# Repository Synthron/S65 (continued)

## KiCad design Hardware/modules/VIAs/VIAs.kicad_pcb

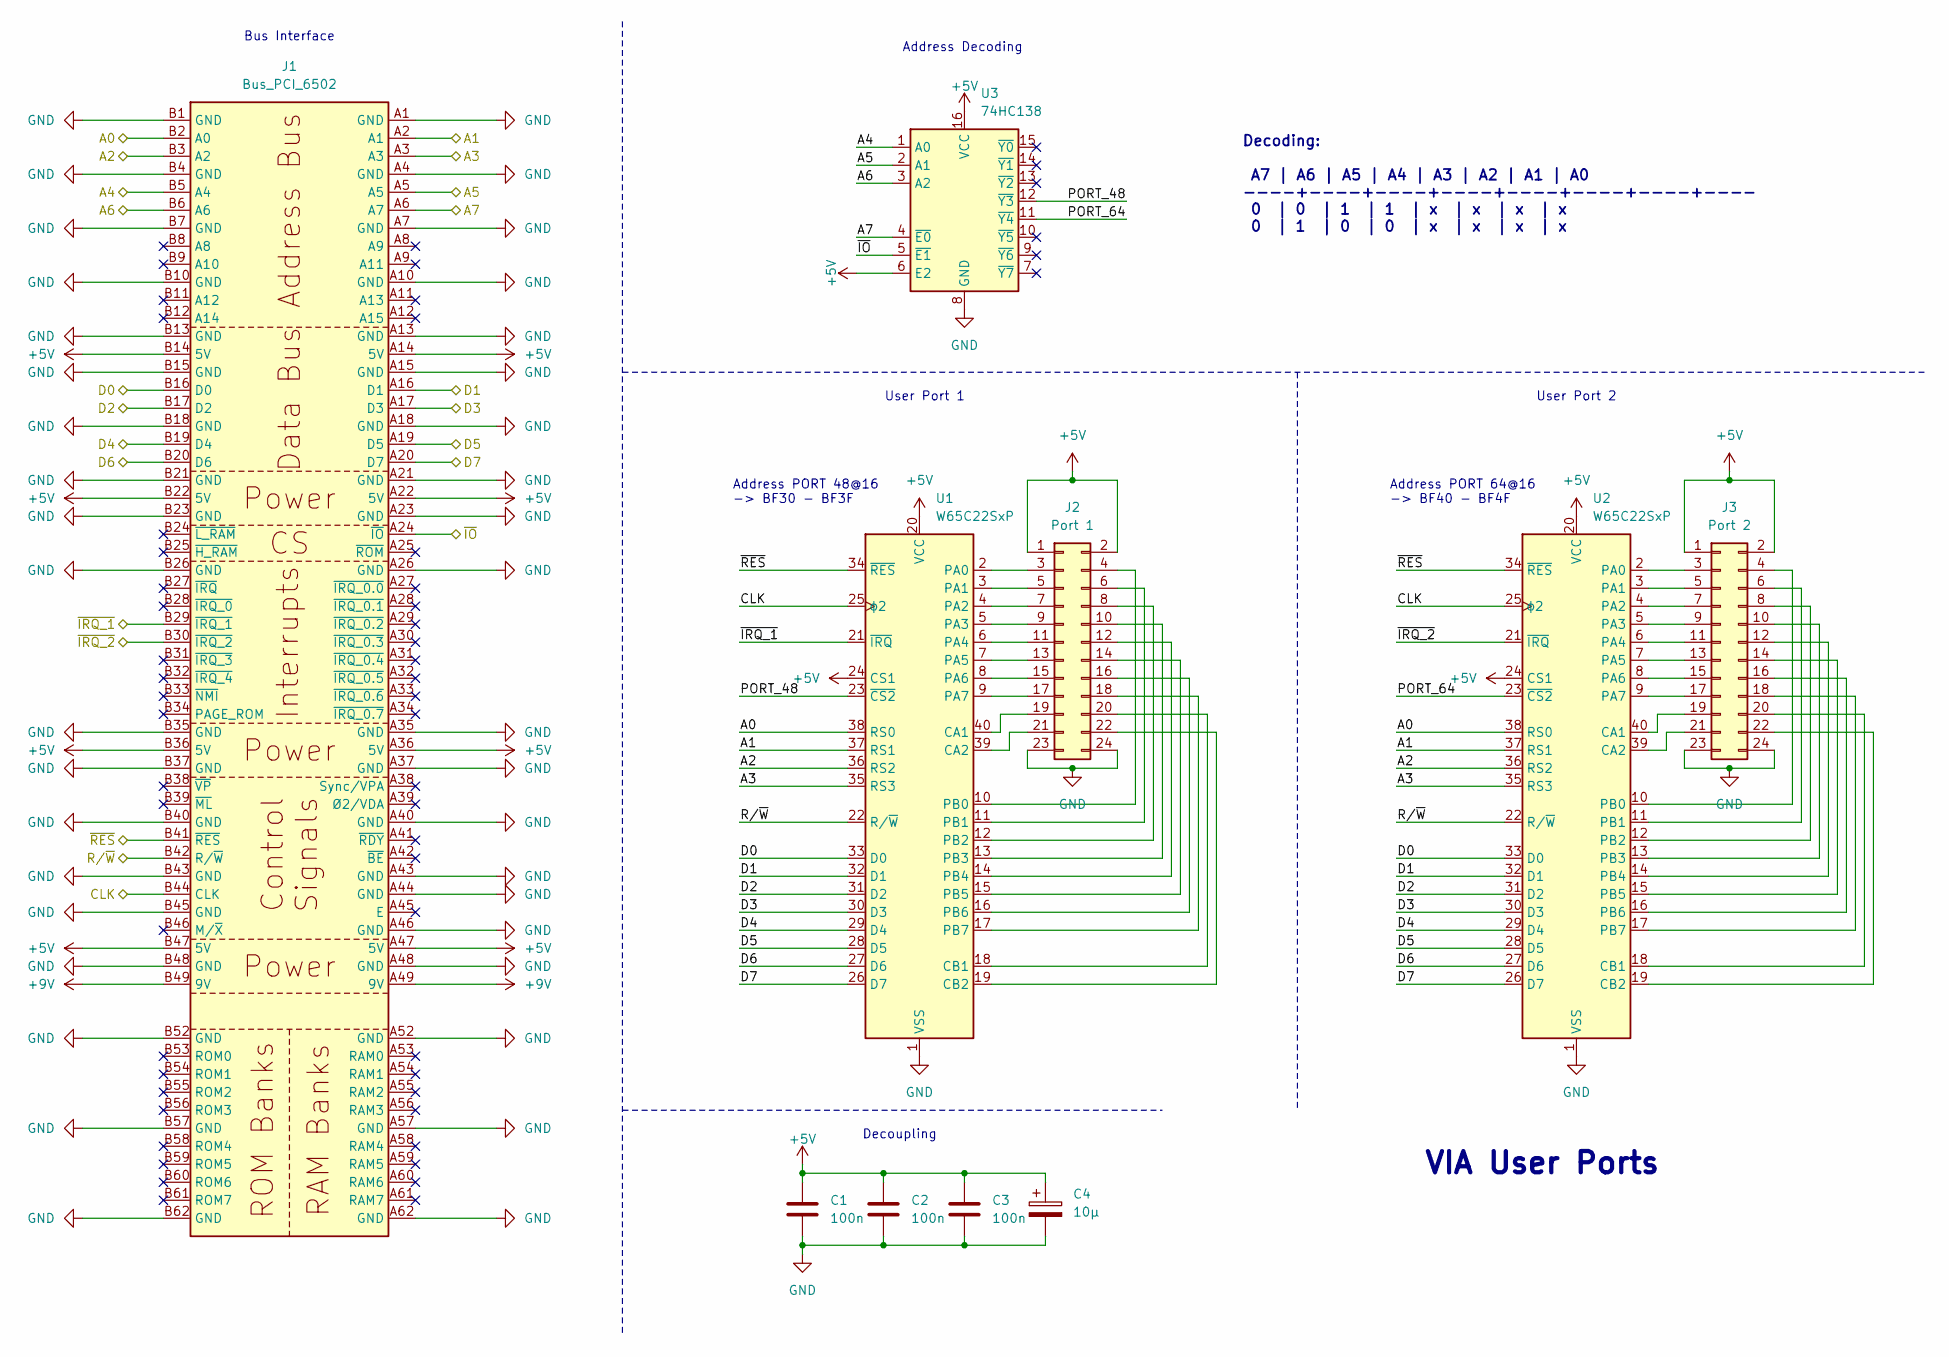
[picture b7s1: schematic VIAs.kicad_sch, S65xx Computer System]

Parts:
C1, C2, C3: 100n; C_0805_2012Metric
C4: 10µ; CP_Radial_D5.0mm_P2.50mm
J1: Bus_PCI_6502; BUS_PCI
J2: Port 1; Pin_Header_2x12
J3: Port 2; Pin_Header_2x12
U1, U2: W65C22SxP; DIP-40_W15.24mm
U3: 74HC138; DIP-16_W7.62mm_LongPads

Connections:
+5V: C1.1, C2.1, C3.1, C4.1, J1.A14 (5V), J1.A22 (5V), J1.A36 (5V), J1.A47 (5V), J1.B14 (5V), J1.B22 (5V), J1.B36 (5V), J1.B47 (5V), J2.1, J2.2, J3.1, J3.2, U1.20 (VCC), U1.24 (CS1), U2.20 (VCC), U2.24 (CS1), U3.6 (E2), U3.16 (VCC)
+9V: J1.A49 (9V), J1.B49 (9V)
/A0: J1.B2 (A0), U1.38 (RS0), U2.38 (RS0)
/A1: J1.A2 (A1), U1.37 (RS1), U2.37 (RS1)
/A2: J1.B3 (A2), U1.36 (RS2), U2.36 (RS2)
/A3: J1.A3, U1.35 (RS3), U2.35 (RS3)
/A4: J1.B5 (A4), U3.1 (A0)
/A5: J1.A5, U3.2 (A1)
/A6: J1.B6 (A6), U3.3 (A2)
/A7: J1.A6 (A7), U3.4 (~E0)
/CLK: J1.B44 (CLK), U1.25 (ϕ2), U2.25 (ϕ2)
/D0: J1.B16 (D0), U1.33 (D0), U2.33 (D0)
/D1: J1.A16 (D1), U1.32 (D1), U2.32 (D1)
/D2: J1.B17 (D2), U1.31 (D2), U2.31 (D2)
/D3: J1.A17 (D3), U1.30 (D3), U2.30 (D3)
/D4: J1.B19 (D4), U1.29 (D4), U2.29 (D4)
/D5: J1.A19 (D5), U1.28 (D5), U2.28 (D5)
/D6: J1.B20 (D6), U1.27 (D6), U2.27 (D6)
/D7: J1.A20 (D7), U1.26 (D7), U2.26 (D7)
/PORT_48: U1.23 (~CS2), U3.12 (~Y3)
/PORT_64: U2.23 (~CS2), U3.11 (~Y4)
/R/~W: J1.B42 (R/~W), U1.22 (R/~W), U2.22 (R/~W)
/~IO: J1.A24 (~IO), U3.5 (~E1)
/~IRQ_1: J1.B29 (~IRQ_1), U1.21 (~IRQ)
/~IRQ_2: J1.B30 (~IRQ_2), U2.21 (~IRQ)
/~RES: J1.B41 (~RES), U1.34 (~RES), U2.34 (~RES)
GND: C1.2, C2.2, C3.2, C4.2, J1.A1 (GND), J1.A4 (GND), J1.A7 (GND), J1.A10 (GND), J1.A13 (GND), J1.A15 (GND), J1.A18 (GND), J1.A21 (GND), J1.A23 (GND), J1.A26 (GND), J1.A35 (GND), J1.A37 (GND), J1.A40 (GND), J1.A43 (GND), J1.A44 (GND), J1.A46 (GND), J1.A48 (GND), J1.A52 (GND), J1.A57 (GND), J1.A62 (GND), J1.B1 (GND), J1.B4 (GND), J1.B7 (GND), J1.B10 (GND), J1.B13 (GND), J1.B15 (GND), J1.B18 (GND), J1.B21 (GND), J1.B23 (GND), J1.B26 (GND), J1.B35 (GND), J1.B37 (GND), J1.B40 (GND), J1.B43 (GND), J1.B45 (GND), J1.B48 (GND), J1.B52 (GND), J1.B57 (GND), J1.B62 (GND), J2.23, J2.24, J3.23, J3.24, U1.1 (VSS), U2.1 (VSS), U3.8 (GND)
unnamed: J2.3, U1.2 (PA0)
unnamed: J2.4, U1.10 (PB0)
unnamed: J2.5, U1.3 (PA1)
unnamed: J2.6, U1.11 (PB1)
unnamed: J2.7, U1.4 (PA2)
unnamed: J2.8, U1.12 (PB2)
unnamed: J2.9, U1.5 (PA3)
unnamed: J2.10, U1.13 (PB3)
unnamed: J2.11, U1.6 (PA4)
unnamed: J2.12, U1.14 (PB4)
unnamed: J2.13, U1.7 (PA5)
unnamed: J2.14, U1.15 (PB5)
unnamed: J2.15, U1.8 (PA6)
unnamed: J2.16, U1.16 (PB6)
unnamed: J2.17, U1.9 (PA7)
unnamed: J2.18, U1.17 (PB7)
unnamed: J2.19, U1.40 (CA1)
unnamed: J2.20, U1.18 (CB1)
unnamed: J2.21, U1.39 (CA2)
unnamed: J2.22, U1.19 (CB2)
unnamed: J3.3, U2.2 (PA0)
unnamed: J3.4, U2.10 (PB0)
unnamed: J3.5, U2.3 (PA1)
unnamed: J3.6, U2.11 (PB1)
unnamed: J3.7, U2.4 (PA2)
unnamed: J3.8, U2.12 (PB2)
unnamed: J3.9, U2.5 (PA3)
unnamed: J3.10, U2.13 (PB3)
unnamed: J3.11, U2.6 (PA4)
unnamed: J3.12, U2.14 (PB4)
unnamed: J3.13, U2.7 (PA5)
unnamed: J3.14, U2.15 (PB5)
unnamed: J3.15, U2.8 (PA6)
unnamed: J3.16, U2.16 (PB6)
unnamed: J3.17, U2.9 (PA7)
unnamed: J3.18, U2.17 (PB7)
unnamed: J3.19, U2.40 (CA1)
unnamed: J3.20, U2.18 (CB1)
unnamed: J3.21, U2.39 (CA2)
unnamed: J3.22, U2.19 (CB2)

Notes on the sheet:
Bus Interface
Address PORT 64@16 -> BF40 - BF4F
Decoding: A7 | A6 | A5 | A4 | A3 | A2 | A1 | A0 ----+----+----+----+----+----+----+---- 0 | 0 | 1 | 1 | x | x | x | x 0 | 1 | 0 | 0 | x | x | x | x
User Port 1
Address Decoding
Decoupling
VIA User Ports
User Port 2
Address PORT 48@16 -> BF30 - BF3F

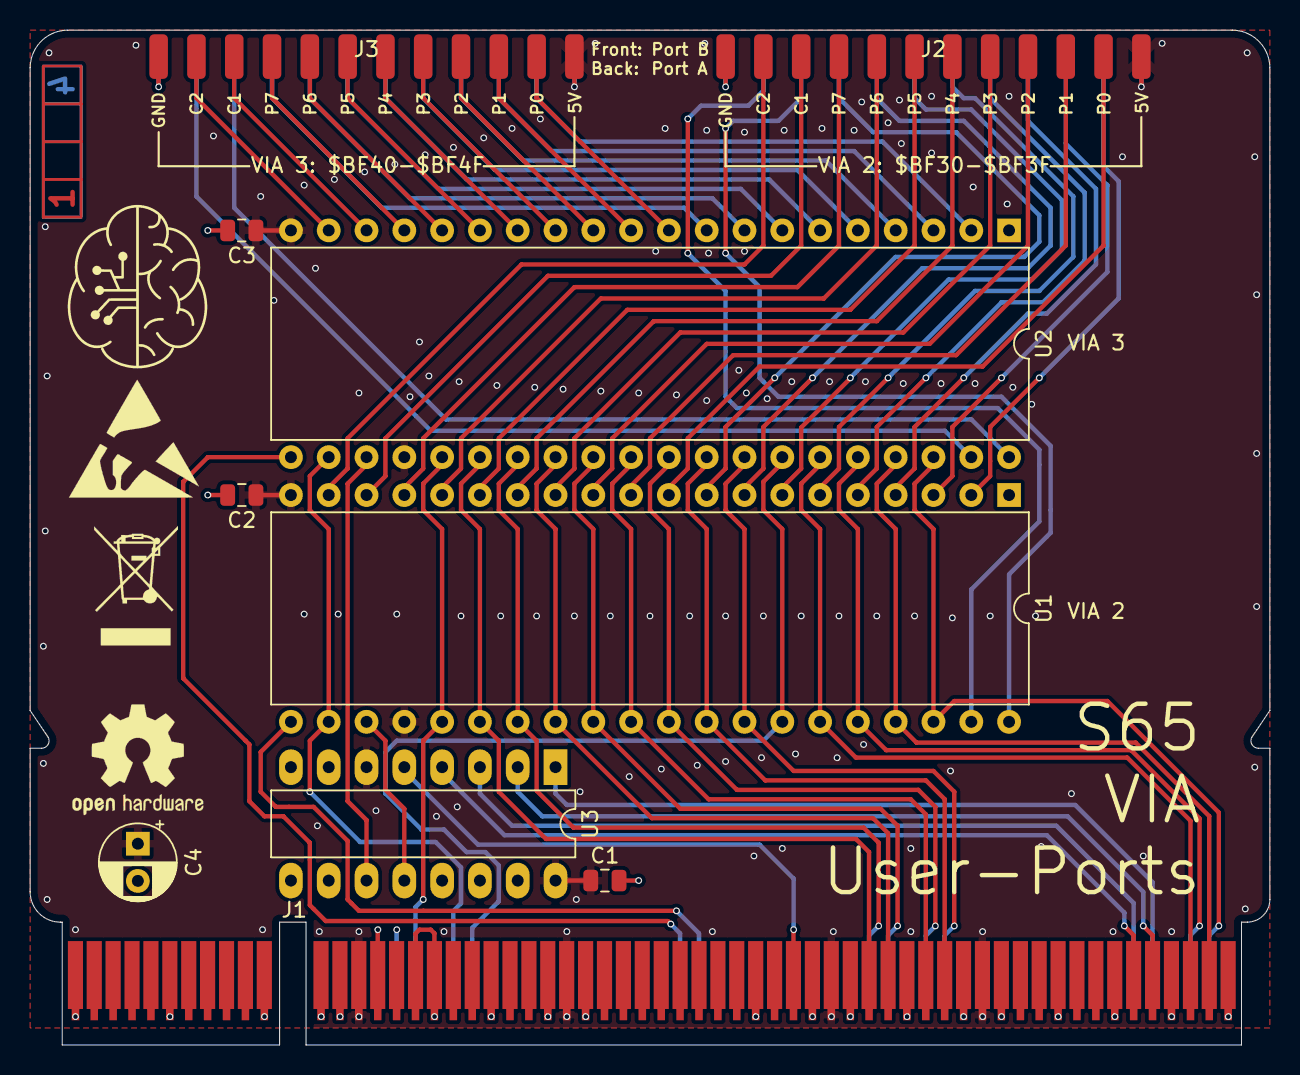
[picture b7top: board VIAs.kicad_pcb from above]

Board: 4 copper layers, 83.3 x 68.2 mm, 11 parts (1 on the bottom side), 67 nets.

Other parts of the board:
Ref**: Val**; ladder_4

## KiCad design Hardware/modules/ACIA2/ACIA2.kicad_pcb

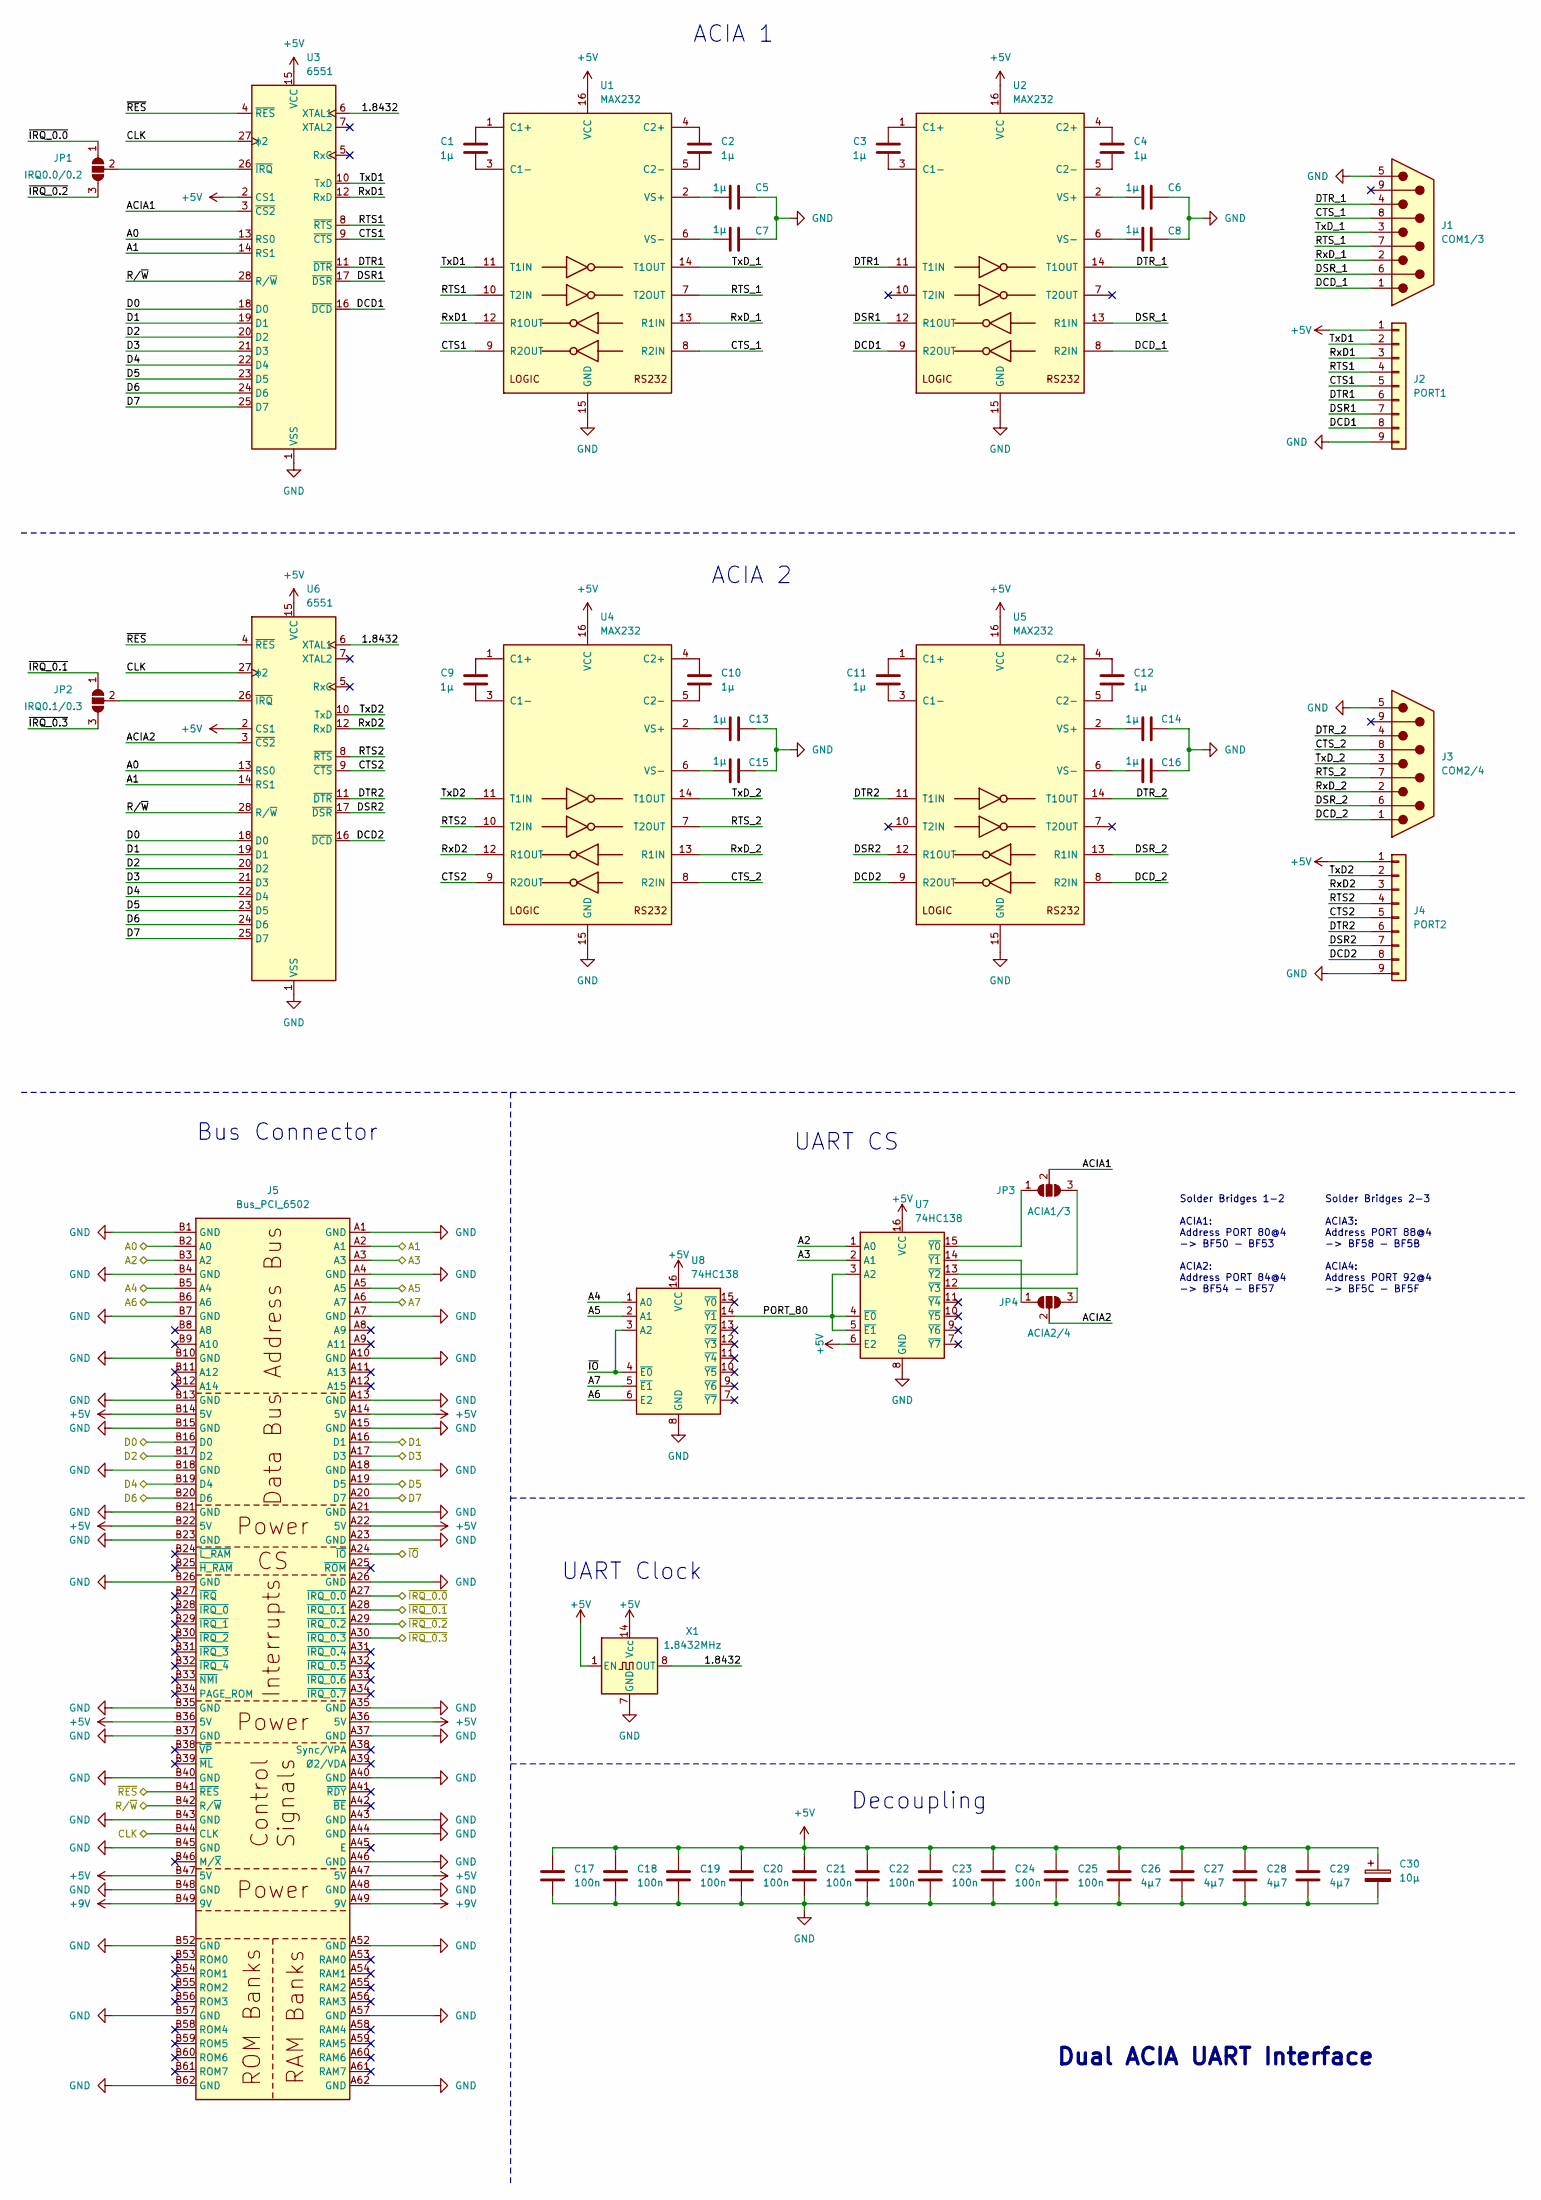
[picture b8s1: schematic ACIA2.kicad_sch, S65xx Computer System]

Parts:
C1, C2, C3, C4, C5, C6, C7, C8, C9, C10, C11, C12, C13, C14, C15, C16: 1µ; C_0805_2012Metric
C17, C18, C19, C20, C21, C22, C23, C24, C25: 100n; C_0805_2012Metric
C26, C27, C28, C29: 4µ7; C_0805_2012Metric
C30: 10µ; CP_Radial_D5.0mm_P2.50mm
J1: COM1/3; DSUB-9_Male_EdgeMount_P2.77mm
J2: PORT1; PinHeader_1x09_P2.54mm_Vertical
J3: COM2/4; DSUB-9_Male_EdgeMount_P2.77mm
J4: PORT2; PinHeader_1x09_P2.54mm_Vertical
J5: Bus_PCI_6502; BUS_PCI
JP1: IRQ0.0/0.2; SolderJumper-3_P2.0mm_Open_TrianglePad1.0x1.5mm_NumberLabels
JP2: IRQ0.1/0.3; SolderJumper-3_P2.0mm_Open_TrianglePad1.0x1.5mm_NumberLabels
JP3: ACIA1/3; SolderJumper-3_P2.0mm_Open_TrianglePad1.0x1.5mm_NumberLabels
JP4: ACIA2/4; SolderJumper-3_P2.0mm_Open_TrianglePad1.0x1.5mm_NumberLabels
U1, U2, U4, U5: MAX232; DIP-16_W7.62mm
U3, U6: 6551; DIP-28_W15.24mm
U7, U8: 74HC138; DIP-16_W7.62mm
X1: 1.8432MHz; Oscillator_DIP-14

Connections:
+5V: C17.1, C18.1, C19.1, C20.1, C21.1, C22.1, C23.1, C24.1, C25.1, C26.1, C27.1, C28.1, C29.1, C30.1, J2.1, J4.1, J5.A14 (5V), J5.A22 (5V), J5.A36 (5V), J5.A47 (5V), J5.B14 (5V), J5.B22 (5V), J5.B36 (5V), J5.B47 (5V), U1.16 (VCC), U2.16 (VCC), U3.2 (CS1), U3.15 (VCC), U4.16 (VCC), U5.16 (VCC), U6.2 (CS1), U6.15 (VCC), U7.6 (E2), U7.16 (VCC), U8.16 (VCC), X1.1 (EN), X1.14 (Vcc)
+9V: J5.A49 (9V), J5.B49 (9V)
/1.8432: U3.6 (XTAL1), U6.6 (XTAL1), X1.8 (OUT)
/A0: J5.B2 (A0), U3.13 (RS0), U6.13 (RS0)
/A1: J5.A2 (A1), U3.14 (RS1), U6.14 (RS1)
/A2: J5.B3 (A2), U7.1 (A0)
/A3: J5.A3, U7.2 (A1)
/A4: J5.B5 (A4), U8.1 (A0)
/A5: J5.A5, U8.2 (A1)
/A6: J5.B6 (A6), U8.6 (E2)
/A7: J5.A6 (A7), U8.5 (~E1)
/ACIA1: JP3.2 (C), U3.3 (~CS2)
/ACIA2: JP4.2 (C), U6.3 (~CS2)
/CLK: J5.B44 (CLK), U3.27 (ϕ2), U6.27 (ϕ2)
/CTS1: J2.5, U1.9 (R2OUT), U3.9 (~CTS)
/CTS2: J4.5, U4.9 (R2OUT), U6.9 (~CTS)
/CTS_1: J1.8, U1.8 (R2IN)
/CTS_2: J3.8, U4.8 (R2IN)
/D0: J5.B16 (D0), U3.18 (D0), U6.18 (D0)
/D1: J5.A16 (D1), U3.19 (D1), U6.19 (D1)
/D2: J5.B17 (D2), U3.20 (D2), U6.20 (D2)
/D3: J5.A17 (D3), U3.21 (D3), U6.21 (D3)
/D4: J5.B19 (D4), U3.22 (D4), U6.22 (D4)
/D5: J5.A19 (D5), U3.23 (D5), U6.23 (D5)
/D6: J5.B20 (D6), U3.24 (D6), U6.24 (D6)
/D7: J5.A20 (D7), U3.25 (D7), U6.25 (D7)
/DCD1: J2.8, U2.9 (R2OUT), U3.16 (~DCD)
/DCD2: J4.8, U5.9 (R2OUT), U6.16 (~DCD)
/DCD_1: J1.1, U2.8 (R2IN)
/DCD_2: J3.1, U5.8 (R2IN)
/DSR1: J2.7, U2.12 (R1OUT), U3.17 (~DSR)
/DSR2: J4.7, U5.12 (R1OUT), U6.17 (~DSR)
/DSR_1: J1.6, U2.13 (R1IN)
/DSR_2: J3.6, U5.13 (R1IN)
/DTR1: J2.6, U2.11 (T1IN), U3.11 (~DTR)
/DTR2: J4.6, U5.11 (T1IN), U6.11 (~DTR)
/DTR_1: J1.4, U2.14 (T1OUT)
/DTR_2: J3.4, U5.14 (T1OUT)
/PORT_80: U7.3 (A2), U7.4 (~E0), U7.5 (~E1), U8.14 (~Y1)
/RTS1: J2.4, U1.10 (T2IN), U3.8 (~RTS)
/RTS2: J4.4, U4.10 (T2IN), U6.8 (~RTS)
/RTS_1: J1.7, U1.7 (T2OUT)
/RTS_2: J3.7, U4.7 (T2OUT)
/RxD1: J2.3, U1.12 (R1OUT), U3.12 (RxD)
/RxD2: J4.3, U4.12 (R1OUT), U6.12 (RxD)
/RxD_1: J1.2, U1.13 (R1IN)
/RxD_2: J3.2, U4.13 (R1IN)
/R/~W: J5.B42 (R/~W), U3.28 (R/~W), U6.28 (R/~W)
/TxD1: J2.2, U1.11 (T1IN), U3.10 (TxD)
/TxD2: J4.2, U4.11 (T1IN), U6.10 (TxD)
/TxD_1: J1.3, U1.14 (T1OUT)
/TxD_2: J3.3, U4.14 (T1OUT)
/~IO: J5.A24 (~IO), U8.3 (A2), U8.4 (~E0)
/~IRQ_0.0: J5.A27 (~IRQ_0.0), JP1.1 (A)
/~IRQ_0.1: J5.A28 (~IRQ_0.1), JP2.1 (A)
/~IRQ_0.2: J5.A29 (~IRQ_0.2), JP1.3 (B)
/~IRQ_0.3: J5.A30 (~IRQ_0.3), JP2.3 (B)
/~RES: J5.B41 (~RES), U3.4 (~RES), U6.4 (~RES)
GND: C5.2, C6.2, C7.2, C8.2, C13.2, C14.2, C15.2, C16.2, C17.2, C18.2, C19.2, C20.2, C21.2, C22.2, C23.2, C24.2, C25.2, C26.2, C27.2, C28.2, C29.2, C30.2, J1.5, J2.9, J3.5, J4.9, J5.A1 (GND), J5.A4 (GND), J5.A7 (GND), J5.A10 (GND), J5.A13 (GND), J5.A15 (GND), J5.A18 (GND), J5.A21 (GND), J5.A23 (GND), J5.A26 (GND), J5.A35 (GND), J5.A37 (GND), J5.A40 (GND), J5.A43 (GND), J5.A44 (GND), J5.A46 (GND), J5.A48 (GND), J5.A52 (GND), J5.A57 (GND), J5.A62 (GND), J5.B1 (GND), J5.B4 (GND), J5.B7 (GND), J5.B10 (GND), J5.B13 (GND), J5.B15 (GND), J5.B18 (GND), J5.B21 (GND), J5.B23 (GND), J5.B26 (GND), J5.B35 (GND), J5.B37 (GND), J5.B40 (GND), J5.B43 (GND), J5.B45 (GND), J5.B48 (GND), J5.B52 (GND), J5.B57 (GND), J5.B62 (GND), U1.15 (GND), U2.15 (GND), U3.1 (VSS), U4.15 (GND), U5.15 (GND), U6.1 (VSS), U7.8 (GND), U8.8 (GND), X1.7 (GND)
unnamed: JP1.2 (C), U3.26 (~IRQ)
unnamed: JP2.2 (C), U6.26 (~IRQ)
unnamed: JP3.1 (A), U7.15 (~Y0)
unnamed: JP3.3 (B), U7.13 (~Y2)
unnamed: JP4.1 (A), U7.14 (~Y1)
unnamed: JP4.3 (B), U7.12 (~Y3)
unnamed: C1.1, U1.1 (C1+)
unnamed: C1.2, U1.3 (C1-)
unnamed: C2.1, U1.4 (C2+)
unnamed: C2.2, U1.5 (C2-)
unnamed: C5.1, U1.2 (VS+)
unnamed: C7.1, U1.6 (VS-)
unnamed: C3.1, U2.1 (C1+)
unnamed: C3.2, U2.3 (C1-)
unnamed: C4.1, U2.4 (C2+)
unnamed: C4.2, U2.5 (C2-)
unnamed: C6.1, U2.2 (VS+)
unnamed: C8.1, U2.6 (VS-)
unnamed: C9.1, U4.1 (C1+)
unnamed: C9.2, U4.3 (C1-)
unnamed: C10.1, U4.4 (C2+)
unnamed: C10.2, U4.5 (C2-)
unnamed: C13.1, U4.2 (VS+)
unnamed: C15.1, U4.6 (VS-)
unnamed: C11.1, U5.1 (C1+)
unnamed: C11.2, U5.3 (C1-)
unnamed: C12.1, U5.4 (C2+)
unnamed: C12.2, U5.5 (C2-)
unnamed: C14.1, U5.2 (VS+)
unnamed: C16.1, U5.6 (VS-)

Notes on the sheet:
Bus Connector
Solder Bridges 1-2 ACIA1: Address PORT 80@4 -> BF50 - BF53 ACIA2: Address PORT 84@4 -> BF54 - BF57
Dual ACIA UART Interface
ACIA 1
UART Clock
Decoupling
Solder Bridges 2-3 ACIA3: Address PORT 88@4 -> BF58 - BF5B ACIA4: Address PORT 92@4 -> BF5C - BF5F
ACIA 2
UART CS

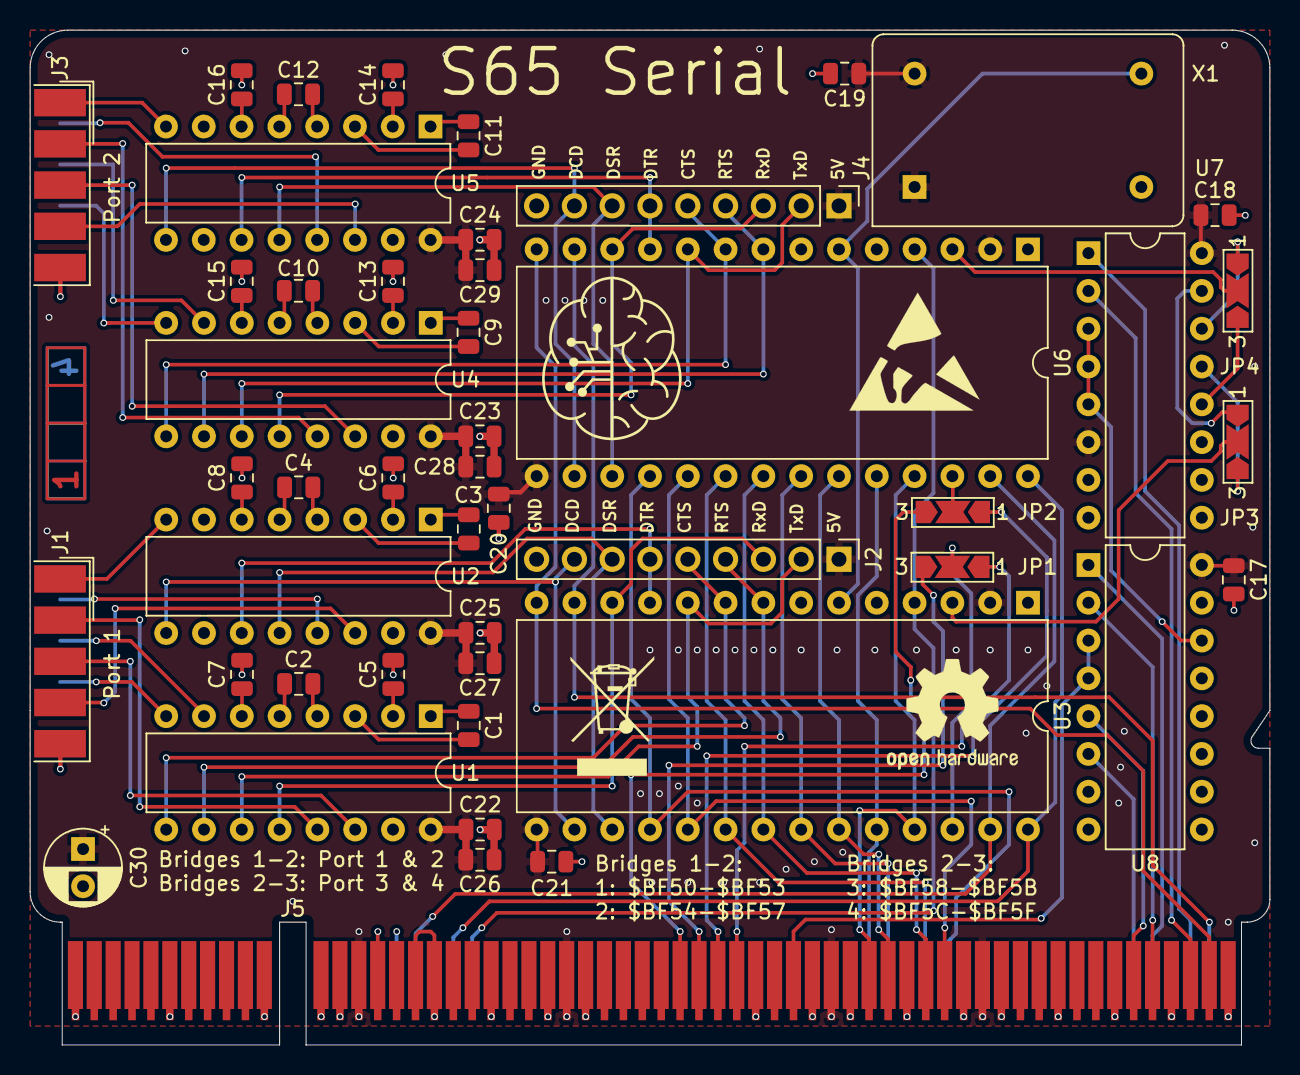
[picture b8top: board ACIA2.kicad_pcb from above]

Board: 4 copper layers, 83.3 x 68.2 mm, 49 parts (1 on the bottom side), 89 nets.

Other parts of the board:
Ref**: Val**; ladder_4

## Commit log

2024-05-28 initial data
2024-06-03 update schematics
2024-06-16 make overview-schematic
2024-06-16 finalize Schematic
2024-06-17 Overview Update and Backplane
2024-06-18 ROM and CPU Card
2024-06-20 module update
2024-06-23 Update Module Files and Readme
2024-06-23 update Silkscreen Bank/IRQ Card
2024-06-24 new modules and readme update
2024-06-25 Big Hardware Update
2024-06-25 polish bus card
2024-06-25 add PCB Clamp
2024-06-26 add LPT
2024-06-30 Hardware Update Add MyCPU VGA Module Beautify all Schematics minor Error corrections Readme Update
2024-06-30 finalize overview schematic
2024-06-30 update Reade
2024-06-30 Fix mirroring on High-Ram on Bank Select
2024-06-30 fix pcb outline
2024-07-01 start codebase write peripheral libraries port wozmon from Ben Eater start Kernel Development start EhBASIC porting
2024-07-01 fix errors in EhBASIC preventing from compilation
2024-07-01 add sample code for jump vector
2024-07-02 code update
2024-07-03 add macro file
2024-07-03 add MS BASIC to code
2024-07-03 msbasic update
2024-07-06 update CPU design to reference WDC design
2024-07-06 recompile code
2024-07-06 Bus Card Update & GAL code compilation
2024-07-07 add local ground plane on 32kHz crystal
2024-07-07 update overview PDF annotation
2024-07-09 Chip Select Strobe Generation Bugfix
2024-07-10 Hardware Review Pt. 1 fix Address Decoding for Strobe Generators add bulk capacitance to every board fix wiring of Prototyping Board
2024-07-11 update overview
2024-07-11 update address decode
2024-07-11 update readme after review
2024-07-26 Big Review Update - Changed Copper Pours on all PCBs - Implemented errors found at review - fixed some additional errors
